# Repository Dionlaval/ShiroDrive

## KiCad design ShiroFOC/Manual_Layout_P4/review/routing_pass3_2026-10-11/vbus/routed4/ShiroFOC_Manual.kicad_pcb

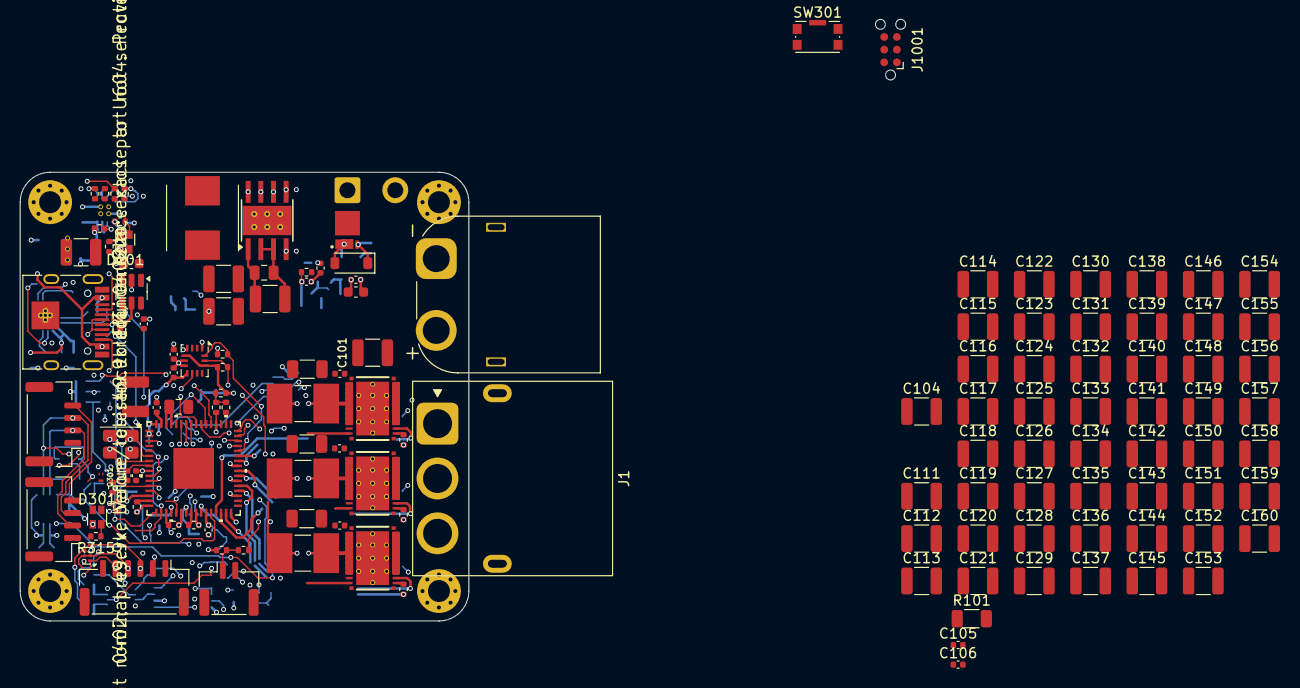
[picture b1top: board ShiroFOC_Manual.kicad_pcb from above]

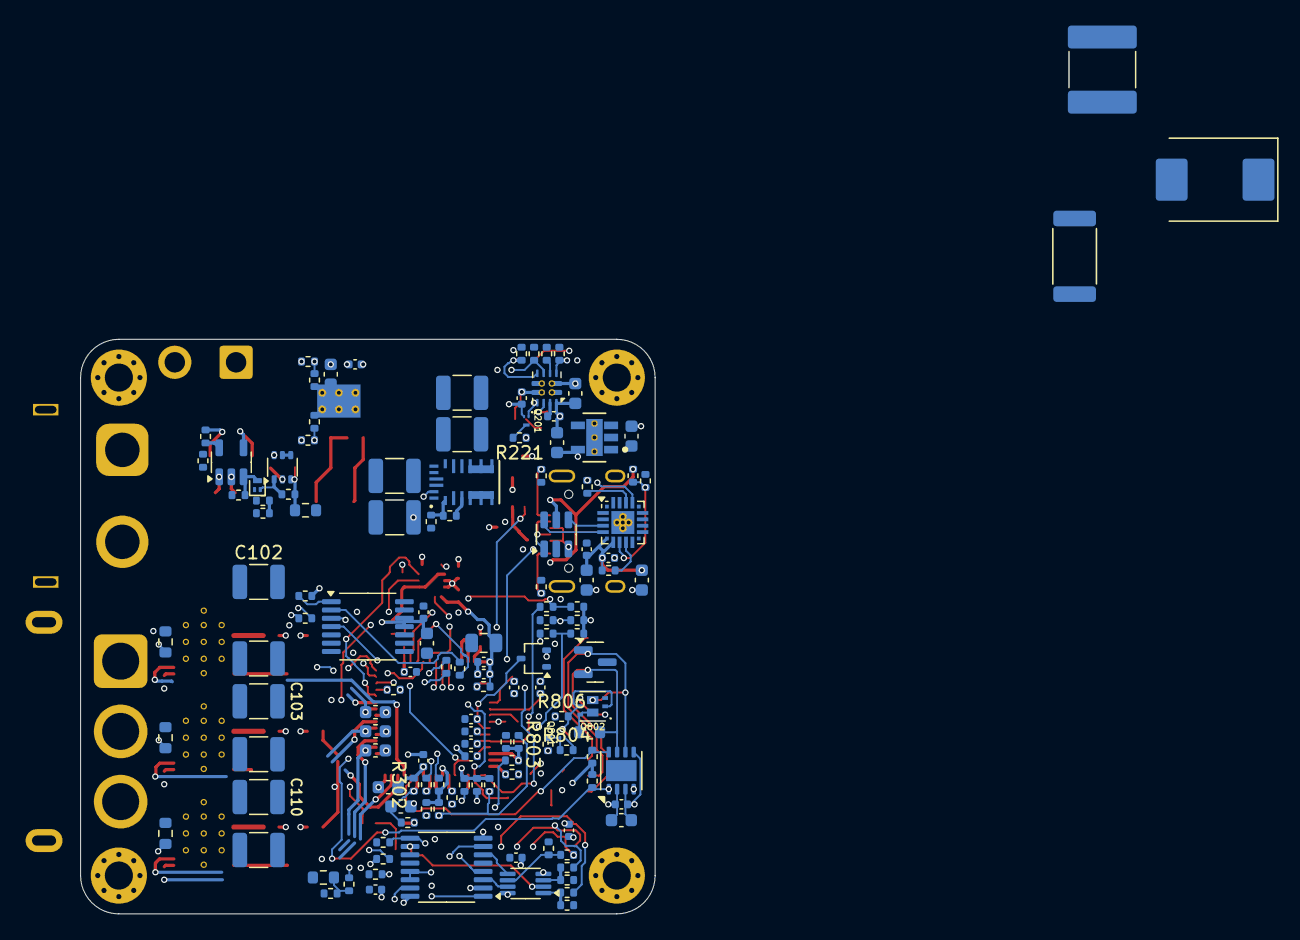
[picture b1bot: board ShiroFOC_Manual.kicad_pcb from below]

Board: 6 copper layers, 45.0 x 45.0 mm, 272 parts (135 on the bottom side), 146 nets.

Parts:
C1, C5, C9, C108, C314, C711, C712, C713: 10nF; C_0402_1005Metric
C2, C6, C10: 1uF; C_1206_3216Metric
C3, C7, C11: 4.7uF; C_1210_3225Metric
C4, C8, C12: 220nF; C_0603_1608Metric
C101, C102, C103, C110, C111, C112, C113, C114, C115, C116, C117, C118, C119, C120, C121, C122, C123, C124, C127, C128, C129, C130, C131, C132, C133, C134, C135, C136, C137, C138, C139, C140, C141, C144, C145, C146, C147, C148, C149, C150, C151, C152, C153, C154, C155, C156, C157, C158: 10uF; C_1210_3225Metric
C104: 4.7uF 100V X7R; C_1210_3225Metric
C105: 100nF 100V X7R; C_0402_1005Metric
C106: 10nF 100V C0G; C_0402_1005Metric
C107: RC DAMP C - TUNE; C_2220_5750Metric
C125, C126, C142, C143, C159, C160: 10uF DNP; C_1210_3225Metric
C201: 2.2uF 100V X7R; C_1210_3225Metric
C202: 220nF 100V X7R; C_0805_2012Metric
C203, C209, C211, C301, C303, C305, C307, C310, C601, C603, C605, C701, C702, C801, C902, C904: 100nF; C_0402_1005Metric
C204, C304, C306, C602, C802: 1uF; C_0603_1608Metric
C205, C206, C214, C215: 22uF 25V X7R; C_1210_3225Metric
C208: 1uF 10V; C_0603_1608Metric
C210: 22uF 10V X7R; C_1210_3225Metric
C212, C213: 2.2uF 10V X7R; C_0603_1608Metric
C218, C219: 22uF 16V X7R; C_1210_3225Metric
C302: 10uF 10V; C_0805_2012Metric
C308, C309: 10pF C0G; C_0402_1005Metric
C311: 220nF 100V; C_0805_2012Metric
C312: 10uF 25V X7R; C_1210_3225Metric
C313: 100nF 25V; C_0402_1005Metric
C501: 1uF 25V; C_0603_1608Metric
C502, C503, C604: 100nF 50V; C_0402_1005Metric
C504: 1nF C0G; C_0402_1005Metric
C505: 100nF 16V; C_0402_1005Metric
C606: 4.7uF 16V X7R; C_0603_1608Metric
C607: 100nF 16V X7R; C_0402_1005Metric
C901, C903: 4.7uF 10V; C_0603_1608Metric
D101: VM TVS - SELECT AFTER TEST; D_SMC
D201, D301: LTST-C19HE1WT; LED_LiteOn_LTST-C19HE1WT
D501: BZT52C12 12V; D_SOD-123
D502: BAT54CM; SOT-883
D505: BAT54SW; SOT-323_SC-70
D601: TPD3E001DRYR; TPD3E001_DRY6
D801: PESD2CANFD24V-T; SOT-23
H1, H2, H3, H4: M2 PTH; MountingHole_2.2mm_M2_Pad_Via
J1: MR60PW-M; AMASS_MR60PW-M_1x03_P5.50mm_Horizontal
J101: AMASS XT60PW-M; AMASS_XT60PW-M_1x02_P7.20mm_Horizontal
J201: USB-C service; USB_C_Receptacle_HRO_TYPE-C-31-M-12
J501: BRAKE RESISTOR; SolderWire-0.75sqmm_1x02_P4.8mm_D1.25mm_OD2.3mm
J502: BRAKE NTC; JST_GH_SM02B-GHS-TB_1x02-1MP_P1.25mm_Horizontal
J601: EXT ENCODER / HALL; JST_GH_BM06B-GHS-TBT_1x06-1MP_P1.25mm_Vertical
J801: CAN 1; JST_GH_BM04B-GHS-TBT_1x04-1MP_P1.25mm_Vertical
J802: CAN 2; JST_GH_BM04B-GHS-TBT_1x04-1MP_P1.25mm_Vertical
J1001: TC2030-NL SWD; Tag-Connect_TC2030-IDC-NL_2x03_P1.27mm_Vertical
L201: 47uH / 1.9A; WE_LHMI_7050_74437349470
Q201, Q301, Q801: CSD17483F4; CSD17483F4_YJC0003A
Q501: ISZ080N10NM6 100V; ISZ080N10NM6_TSDSON8_FL
Q802: CSD87502Q2; CSD87502Q2_DLV0006A
R1, R3, R5: 0.5m 1%; R_Shunt_LR2512D_0m5_3W_Kelvin
R2, R4, R6: 4R7; R_0402_1005Metric
R101: 470k 0.25W; R_1206_3216Metric
R102: RC DAMP R - TUNE; R_2512_6332Metric
R103: 560k 0.1% 75V; R_0603_1608Metric
R105, R419, R429, R439: 28k 0.1%; R_0402_1005Metric
R106, R312, R711, R712, R713, R901: 1k; R_0402_1005Metric
R201: 100k 1%; R_0402_1005Metric
R202: 11.1k 1%; R_0402_1005Metric
R203, R204: 5.1k; R_0402_1005Metric
R206: 15.0k 1%; R_0402_1005Metric
R207, R209, R211, R213: 5.10k 1%; R_0402_1005Metric
R208: 10.0k 1%; R_0402_1005Metric
R210, R212: 22.0k 1%; R_0402_1005Metric
R214: 80.6k 1%; R_0402_1005Metric
R215, R220, R305, R306, R307, R309, R311, R315, R501, R504, R505, R604, R801, R805, R806: 10k; R_0402_1005Metric
R216: 34.0k 0.1%; R_0402_1005Metric
R217: 6.49k 0.1%; R_0402_1005Metric
R218, R219, R310, R615, R616, R617, R804: 100k; R_0402_1005Metric
R221: 33k; R_0402_1005Metric
R301, R302: 0R; R_0402_1005Metric
R303: 2k2; R_0402_1005Metric
R304: 15k; R_0402_1005Metric
R308, R715: 2.2k; R_0402_1005Metric
R313, R314: 22R; R_0402_1005Metric
R410, R420, R430, R441, R442, R443: 56k 0.1%; R_0402_1005Metric
R417, R418, R427, R428, R437, R438: 1k 0.1%; R_0402_1005Metric
R502, R611: 33R; R_0402_1005Metric
R503: 4.7R; R_0402_1005Metric
R506: 470k 1% 75V; R_0603_1608Metric
R509: 13.3k 1%; R_0402_1005Metric
R510: 1M 1%; R_0402_1005Metric
R511: 10k 1%; R_0402_1005Metric
R512, R701, R702, R703: 4.7k 1%; R_0402_1005Metric
R605, R606, R607, R902, R903: 100R; R_0402_1005Metric
R618: 49.9k 1%; R_0402_1005Metric
R802: 120R 1%; R_0603_1608Metric
R803: 4.7k; R_0402_1005Metric
R904: 22.1k 1%; R_0402_1005Metric
R905: 47.5k 1%; R_0402_1005Metric
SW301: RESET; SW_Push_1P1T-SH_NO_CK_KMR2xxG
TH701, TH702, TH703: 10k NTC B3380; R_0603_1608Metric
U1, U2, U3: CSD88599Q5DC; DMM0022A
U4: STSPIN32G4; QFN_IN32G4_STM
U201: LMR36510FADDAR; LMR36510_DDA
U202: USBLC6-2SC6; USBLC6_SOT23_6
U203: TPS2121RUXR; TPS2121_RUX
U204: TLV75533PDYDR; TLV75533_DYD_GND
U205: MPM3620AGQV-Z; IC18_MPM3620AGQV-Z_MNP
U501: UCC27517ADBVR; UCC27517A_DBV5
U502: TLV3012BIDCKR; SOT-363_SC-70-6
U601: AS5047P-ATSM; AS5047P_TSSOP14
U602: TMUX1574PW; TMUX1574_PW16
U603: 74LVC3G17; VSSOP-8_2.3x2mm_P0.5mm
U604: TPS2553DBVR; SOT-23-6
U701: BMI323; BMI323_LGA14
U801: TCAN3413DRBR; TCAN3413_DRB8
U901: CP2102N-A02-GQFN20; SiliconLabs_QFN-20-1EP_3x3mm_P0.5mm_EP1.8x1.8mm_ThermalVias
Y301: 24MHz 7pF; Crystal_SMD_3225-4Pin_3.2x2.5mm

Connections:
3V3: C213.1, C301.1, C302.1, C307.1, C503.1, C601.1, C602.1, C603.1, C605.1, C701.1, C702.1, C801.1, C802.1, C901.1, C902.1, C903.1, C904.1, D505.2 (K), J1001.1 (VCC), R301.1, R303.1, R305.1, R308.1, R309.1, R310.1, R511.1, R604.1, R701.1, R702.1, R703.1, R715.1, R801.1, R805.1, R901.1, U4.1 (REG3V3/VDD), U4.2 (VBAT), U4.64 (REGIN), U204.5 (OUT), U502.6 (VDD), U601.11 (VDD), U601.12 (VDD3V3), U602.16 (VDD), U603.8 (VCC), U701.5 (VDDIO), U701.8 (VDD), U701.12 (CSB), U801.3 (VCC), U801.5 (VIO), U901.6 (VDD), U901.7 (VREGIN)
5V_BAT: C218.1, C219.1, R206.1, R210.1, R216.1, U203.7 (IN1), U205.7 (OUT), U205.8 (OUT), U205.9 (OUT)
5V_SYS: C210.1, C211.1, C212.1, C606.1, D201.4 (A), D301.4 (A), R215.1, U203.1 (OUT), U203.8 (OUT), U204.1 (IN), U204.3 (EN), U604.1 (IN), U604.3 (EN)
5V_USB: C208.1, J201.A4 (VBUS), J201.A9 (VBUS), J201.B4 (VBUS), J201.B9 (VBUS), R208.1, R212.1, R904.1, U202.5 (VBUS), U203.2 (IN2)
/5 V / 3.3 V power/10V_FB: R201.2, R202.1, U201.5 (FB)
/5 V / 3.3 V power/10V_GOOD: R218.2, R219.1, U201.4 (PG), U205.17 (EN)
/5 V / 3.3 V power/U205_AGND: R217.2, U205.3 (AGND)
/5 V / 3.3 V power/U205_SW: U205.4 (SW), U205.5 (SW), U205.6 (SW)
/Brake chopper/BRAKE_NTC_RAW: J502.1, R511.2, R512.1
/Brake chopper/BRAKE_OV_CMD: D502.2 (A2), R510.1, U502.1 (OUT)
/Brake chopper/BRAKE_PWM_DRV: D502.3 (CC), R505.1, U501.3 (IN+)
/CAN interface/CANH_BUS: D801.2 (CANH_IN), J801.2, J802.2, R802.1, U801.7 (CANH)
/CAN interface/CANL_BUS: D801.1 (CANL_IN), J801.3, J802.3, Q802.3 (D2), U801.6 (CANL)
/CAN interface/CAN_SHIELD: J801.4, J802.4
/Current / temperature/NTC_A_RAW: R701.2, R711.1, TH701.1
/Current / temperature/NTC_B_RAW: R702.2, R712.1, TH702.1
/Current / temperature/NTC_C_RAW: R703.2, R713.1, TH703.1
/Current / temperature/OPN_U1: R418.2, R419.2, U4.16 (-)
/Current / temperature/OPN_V1: R428.2, R429.2, U4.22 (-)
/Current / temperature/OPN_W1: R438.2, R439.2, U4.25 (-)
/Current / temperature/OPP_U1: R410.2, R417.2, R441.1, U4.14 (+)
/Current / temperature/OPP_V1: R420.2, R427.2, R442.1, U4.20 (+)
/Current / temperature/OPP_W1: R430.2, R437.2, R443.1, U4.23 (+)
/External feedback/EXT_VCC: C607.1, J601.1, U604.6 (OUT)
/External feedback/FB_ESD_RAIL: C604.1, D601.6 (VCC)
/MCU / clock / SWD/NRST: C310.1, J1001.3 (~RESET), R303.2, SW301.1, U4.8 (PG10/NRST)
/MCU / clock / SWD/SWCLK: J1001.4 (SWCLK), U4.50 (PA14/SWCLK)
/MCU / clock / SWD/SWDIO: J1001.2 (SWDIO), U4.49 (PA13/SWDIO)
/Three-phase bridge/LS_SOURCE_U: R3.1 (POWER+), U1.12 (PGND), U1.13 (PGND), U1.14 (PGND), U1.15 (PGND), U1.16 (PGND), U1.17 (PGND), U1.18 (PGND), U1.19 (PGND), U1.20 (PGND)
/Three-phase bridge/LS_SOURCE_V: R1.1 (POWER+), U2.12 (PGND), U2.13 (PGND), U2.14 (PGND), U2.15 (PGND), U2.16 (PGND), U2.17 (PGND), U2.18 (PGND), U2.19 (PGND), U2.20 (PGND)
/Three-phase bridge/LS_SOURCE_W: R5.1 (POWER+), U3.12 (PGND), U3.13 (PGND), U3.14 (PGND), U3.15 (PGND), U3.16 (PGND), U3.17 (PGND), U3.18 (PGND), U3.19 (PGND), U3.20 (PGND)
/USB service/CP2102_RST_N: R901.2, U901.9 (RST)
/USB service/CP2102_VBUS_SENSE: R904.2, R905.1, U901.8 (VBUS)
/USB service/UART_BRIDGE_RX: R903.2, U901.17 (RXD)
/USB service/UART_BRIDGE_TX: R902.1, U901.18 (TXD)
/USB service/USB_CC1: J201.A5 (CC1), R203.1
/USB service/USB_CC2: J201.B5 (CC2), R204.1
/USB service/USB_DM: U202.6 (IO1), U901.5 (D-)
/USB service/USB_DM_CONN: J201.A7 (D-), J201.B7 (D-), U202.1 (IO1)
/USB service/USB_DP: U202.4 (IO2), U901.4 (D+)
/USB service/USB_DP_CONN: J201.A6 (D+), J201.B6 (D+), U202.3 (IO2)
AS5047P_CS_N: R309.2, U4.51 (PA15), U601.1 (CSn)
BOOTSTRAP1: C4.2, U4.41 (BOOTSTRAP1)
BOOTSTRAP2: C8.2, U4.38 (BOOTSTRAP2)
BOOTSTRAP3: C12.2, U4.35 (BOOTSTRAP3)
BRAKE_PWM: R501.1, R502.1, U4.60 (PB9)
CAN_STB: R801.2, U4.28 (PB10), U801.8 (STB)
CAN_TERM_DISABLE: R803.1, U4.5 (PC15)
CAN_TERM_GATE: Q301.1 (G), Q801.3 (D), Q802.2 (G1), Q802.5 (G2), R806.2
EXT_FEEDBACK_SELECT: R306.1, U4.53 (PD2), U602.1 (SEL)
EXT_SENSOR_FAULT_N: R604.2, U4.3 (PC13), U604.4 (~FAULT)
FDCAN1_RX: U4.47 (PA11), U801.4 (RXD)
FDCAN1_TX: R805.2, U4.48 (PA12), U801.1 (TXD)
FEEDBACK_A_H1: U4.57 (PB6), U602.4 (D1)
FEEDBACK_B_H2: U4.58 (PB7), U602.7 (D2)
FEEDBACK_I_H3: R307.1, U4.59 (PB8/BOOT0), U602.9 (D3)
GHS1: R2.2, U4.43 (GHS1)
GHS2: R4.2, U4.40 (GHS2)
GHS3: R6.2, U4.37 (GHS3)
GLS1: U1.22 (GL), U4.29 (GLS1)
GLS2: U2.22 (GL), U4.30 (GLS2)
GLS3: U3.22 (GL), U4.31 (GLS3)
GND: C1.2, C2.2, C3.2, C5.2, C6.2, C7.2, C9.2, C10.2, C11.2, C101.2, C102.2, C103.2, C104.2, C105.2, C106.2, C107.2, C108.2, C110.2, C111.2, C112.2, C113.2, C114.2, C115.2, C116.2, C117.2, C118.2, C119.2, C120.2, C121.2, C122.2, C123.2, C124.2, C125.2, C126.2, C127.2, C128.2, C129.2, C130.2, C131.2, C132.2, C133.2, C134.2, C135.2, C136.2, C137.2, C138.2, C139.2, C140.2, C141.2, C142.2, C143.2, C144.2, C145.2, C146.2, C147.2, C148.2, C149.2, C150.2, C151.2, C152.2, C153.2, C154.2, C155.2, C156.2, C157.2, C158.2, C159.2, C160.2, C201.2, C202.2, C204.2, C205.2, C206.2, C208.2, C209.2, C210.2, C211.2, C212.2, C213.2, C214.2, C215.2, C218.2, C219.2, C301.2, C302.2, C303.2, C304.2, C305.2, C306.2, C307.2, C308.2, C309.2, C310.2, C311.2, C312.2, C313.2, C314.2, C501.2, C502.2, C503.2, C504.2, C505.2, C601.2, C602.2, C603.2, C604.2, C605.2, C606.2, C607.2, C701.2, C702.2, C711.2, C712.2, C713.2, C801.2, C802.2, C901.2, C902.2, C903.2, C904.2, D101.2 (A), D501.2 (A), D505.1 (A), D601.3 (GND), D801.3 (GND), J101.1, J201.A1 (GND), J201.A12 (GND), J201.B1 (GND), J201.B12 (GND), J201.S1 (SHIELD), J502.2, J502.MP (MOUNT), J601.2, J601.6, J601.MP (MOUNT), J801.1, J801.MP (MOUNT), J802.1, J802.MP (MOUNT), J1001.5 (GND), Q201.2 (S), Q301.2 (S), Q501.1 (S), Q501.2 (S), Q501.3 (S), Q801.2 (S), R1.4 (POWER-), R3.4 (POWER-), R5.4 (POWER-), R101.2, R105.2, R202.2, R203.2, R204.2, R207.2, R209.2, R211.2, R213.2, R214.2, R219.2, R220.2, R306.2, R307.2, R311.2, R315.2, R441.2, R442.2, R443.2, R501.2, R504.2, R505.2, R509.2, R615.2, R616.2, R617.2, R618.2, R804.2, R905.2, SW301.2, SW301.SH (B), TH701.2, TH702.2, TH703.2, U4.32 (PGND), U4.65 (VSS/EP), U201.1 (PGND), U201.9 (GND), U202.2 (GND), U203.12 (GND), U204.2 (GND), U205.12 (PGND), U205.13 (PGND), U205.14 (PGND), U501.2 (GND), U501.4 (IN-), U502.2 (GND), U601.5 (TEST), U601.13 (GND), U602.2 (S1A), U602.5 (S2A), U602.8 (GND), U602.11 (S3A), U603.4 (GND), U604.2 (GND), U701.1 (SDO/SA0), U701.6 (GNDIO), U701.7 (GND), U801.2 (GND), U801.9 (EP), U901.3 (GND), U901.12 (GND), U901.21 (EP), Y301.2, Y301.4
HS_RETURN_U: C4.1, U1.2 (SH), U4.42 (OUT1)
HS_RETURN_V: C8.1, U2.2 (SH), U4.39 (OUT2)
HS_RETURN_W: C12.1, U3.2 (SH), U4.36 (OUT3)
I2C2_SCL: R308.2, U4.21 (PC4), U701.13 (SCK/SCL)
I2C2_SDA: R715.2, U4.44 (PA8), U701.14 (SDI/SDA)
IMU_INT1: U4.17 (PA4), U701.4 (INT1)
IMU_INT2: U4.18 (PA5), U701.9 (INT2)
INPUT_MUX_ENABLE_N: R305.2, U4.4 (PC14), U602.15 (EN_N)
NTC_BRAKE: C505.1, D505.3 (COM), R512.2, U4.10 (PC1)
NTC_PHASE_A: C711.1, R711.2, U4.12 (PC3)
NTC_PHASE_B: C712.1, R712.2, U4.11 (PC2)
NTC_PHASE_C: C713.1, R713.2, U4.13 (PA0)
unnamed: C107.1, R102.2
unnamed: D201.3 (BK), R220.1
unnamed: D201.2 (GK), R221.1
unnamed: D301.3 (BK), R315.1
unnamed: D301.1 (RK), R304.2
unnamed: D501.1 (K), Q501.4 (G), R503.2, R504.1
unnamed: D502.1 (A1), R502.2
unnamed: D601.1 (IO1), J601.5, R607.1
unnamed: D601.2 (IO2), D601.5 (NC), J601.4, R606.1
unnamed: D601.4 (IO3), J601.3, R605.1
unnamed: J501.1, Q501.5 (D), Q501.6 (D), Q501.7 (D), Q501.8 (D)
unnamed: Q201.3 (D), R221.2
unnamed: Q301.3 (D), R304.1
unnamed: Q801.1 (G), R803.2, R804.1
unnamed: Q802.6 (D1), R802.2
unnamed: Q802.1 (S1), Q802.4 (S2)
unnamed: R103.2, R105.1, R106.1
unnamed: R310.2, R311.1, R312.1
unnamed: R605.2, R615.1, U603.1
unnamed: R606.2, R616.1, U603.3
unnamed: R607.2, R617.1, U603.6
unnamed: R2.1, U1.1 (GH)
unnamed: R4.1, U2.1 (GH)
unnamed: R6.1, U3.1 (GH)
unnamed: C308.1, U4.6 (PF0), Y301.1
unnamed: C309.1, U4.7 (PF1), Y301.3
unnamed: C314.1, R312.2, U4.52 (SCREF)
unnamed: C203.1, U201.7 (BOOT)
unnamed: C203.2, L201.1, U201.8 (SW)
unnamed: C204.1, U201.6 (VCC)
unnamed: R208.2, R209.1, U203.3 (CP2)
unnamed: R214.1, U203.10 (ILM)
unnamed: R210.2, R211.1, U203.5 (OV1)
unnamed: R212.2, R213.1, U203.4 (OV2)
unnamed: R206.2, R207.1, U203.6 (PR1)
unnamed: C209.1, U203.11 (SS)
unnamed: R216.2, R217.1, U205.1 (FB)
unnamed: R503.1, U501.5 (OUT)
unnamed: C504.1, R506.2, R509.1, R510.2, U502.3 (IN+)
unnamed: U502.4 (IN-), U502.5 (REF)
unnamed: R313.2, U601.2 (CLK)
unnamed: R611.1, U601.3 (MISO)
unnamed: R314.2, U601.4 (MOSI)
unnamed: U602.3 (S1B), U603.7
unnamed: U602.6 (S2B), U603.5
unnamed: U602.10 (S3B), U603.2
unnamed: R618.1, U604.5 (ILIM)
OPO_U1: R419.1, U4.15 (OUT)
OPO_V1: R429.1, U4.19 (OUT)
OPO_W1: R439.1, U4.24 (OUT)
PHASE_U: J1.1 (U), U1.3 (VSW), U1.4 (VSW), U1.5 (VSW), U1.6 (VSW), U1.7 (VSW), U1.8 (VSW), U1.9 (VSW), U1.10 (VSW), U1.11 (VSW)
PHASE_V: J1.2 (V), U2.3 (VSW), U2.4 (VSW), U2.5 (VSW), U2.6 (VSW), U2.7 (VSW), U2.8 (VSW), U2.9 (VSW), U2.10 (VSW), U2.11 (VSW)
PHASE_W: J1.3 (W), U3.3 (VSW), U3.4 (VSW), U3.5 (VSW), U3.6 (VSW), U3.7 (VSW), U3.8 (VSW), U3.9 (VSW), U3.10 (VSW), U3.11 (VSW)
PWR_SOURCE_STATUS: Q201.1 (G), R215.2, U203.9 (ST)
SHUNT_U_SENSE_N: R3.3 (SENSE-), R418.1
SHUNT_U_SENSE_P: R3.2 (SENSE+), R417.1
SHUNT_V_SENSE_N: R1.3 (SENSE-), R428.1
SHUNT_V_SENSE_P: R1.2 (SENSE+), R427.1
SHUNT_W_SENSE_N: R5.3 (SENSE-), R438.1
SHUNT_W_SENSE_P: R5.2 (SENSE+), R437.1
SPI3_MISO: R611.2, U4.55 (PB4)
SPI3_MOSI_MCU: R314.1, U4.56 (PB5)
SPI3_SCK_MCU: R313.1, U4.54 (PB3)
USB_UART_RX: R902.2, U4.46 (PA10)
USB_UART_TX: R903.1, U4.45 (PA9)
VBUS_MUX_IN: R106.2, U602.13 (S4A), U602.14 (S4B)
VBUS_SENSE: C108.1, U4.9 (PC0), U602.12 (D4)
VCC: C205.1, C206.1, C214.1, C215.1, C312.1, C313.1, C501.1, C502.1, L201.2, R201.1, R218.1, R806.1, U4.63 (VCC), U205.16 (IN), U501.1 (VDD)
VDDA: C303.1, C304.1, R301.2, R302.1, U4.27 (VDDA)
VM: C1.1, C2.1, C3.1, C5.1, C6.1, C7.1, C9.1, C10.1, C11.1, C101.1, C102.1, C103.1, C104.1, C105.1, C106.1, C110.1, C111.1, C112.1, C113.1, C114.1, C115.1, C116.1, C117.1, C118.1, C119.1, C120.1, C121.1, C122.1, C123.1, C124.1, C125.1, C126.1, C127.1, C128.1, C129.1, C130.1, C131.1, C132.1, C133.1, C134.1, C135.1, C136.1, C137.1, C138.1, C139.1, C140.1, C141.1, C142.1, C143.1, C144.1, C145.1, C146.1, C147.1, C148.1, C149.1, C150.1, C151.1, C152.1, C153.1, C154.1, C155.1, C156.1, C157.1, C158.1, C159.1, C160.1, C201.1, C202.1, C311.1, D101.1 (K), J101.2, J501.2, R101.1, R102.1, R103.1, R506.1, U1.27 (VIN), U2.27 (VIN), U3.27 (VIN), U4.61 (VM), U4.62 (SW), U201.2 (VIN), U201.3 (EN)
VREF+: C305.1, C306.1, R302.2, R410.1, R420.1, R430.1, U4.26 (VREF+)
